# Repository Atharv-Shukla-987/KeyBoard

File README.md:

# mech_board
## Introduction
It is compact wireless custum mechanical keyboard based on rasberry pi pico w with a 0.96 Oled display for displaying battery percentage and with a slider[linear potential meter] for music control and some DJ vibes, yes a slider not a rotary encoder because for some reason i just don't like rotary encoders. It has battery of 2000 mah . It can act as wired and wireless keyboard , both . I have a slider switch for changing the mode . It got two holes on its case wall one for charging port and other for pico port . I have also used RGBs for some asthetics. My pc does not have in built blutooth so , I have also made a reciever dougle.
## Components Used
### kerboard
 1.I have used raspberry pi pico w over others because beacause of high number of gpio pins and is easily programable and also is bluetooth and wifi for good contectivity
 2. A TP4050 [charging module] for charging battery
 
 3. A mcp1700 [voltage regulator] for converting 3.7v from battery to 5v requried from raspberry pi pico w
 
 4.A 1N4148 Diode so that ghosting do not occurs 

 5. A oled display 128x64 i2c for checking battery and making keyboard more intresting

 6. A SK6812 MINI for lightening and vibe

 7. A female Usb type C for charging 

 8. A 3.7V 2000mah lipo battery for increased battery life

 9. keycaps from meckeys

 10. custum pcb
 
 11. 3d printed case
 
 12. cherry x switches
 
 13. Capacitors and registors 

### reciever 

1.esp32 mini s3 for conecting with keyboard 

2. USb type A

3. MCP1700 voltage regulator

# RECIEVER

## schematics

## PCB layout

## 3d

### Front

### Back

# KEYBOARD

## schematic

## PCB layout

## 3D 
### front

### back Model

## footprints

## Case

### Top case

### Bottom case

### Assembled case

# BOM 

https://docs.google.com/spreadsheets/d/1NN-7fyjT-_NMtKUpMZtBps8UBcZRbg7seoi4lXChdCc/edit?usp=sharing

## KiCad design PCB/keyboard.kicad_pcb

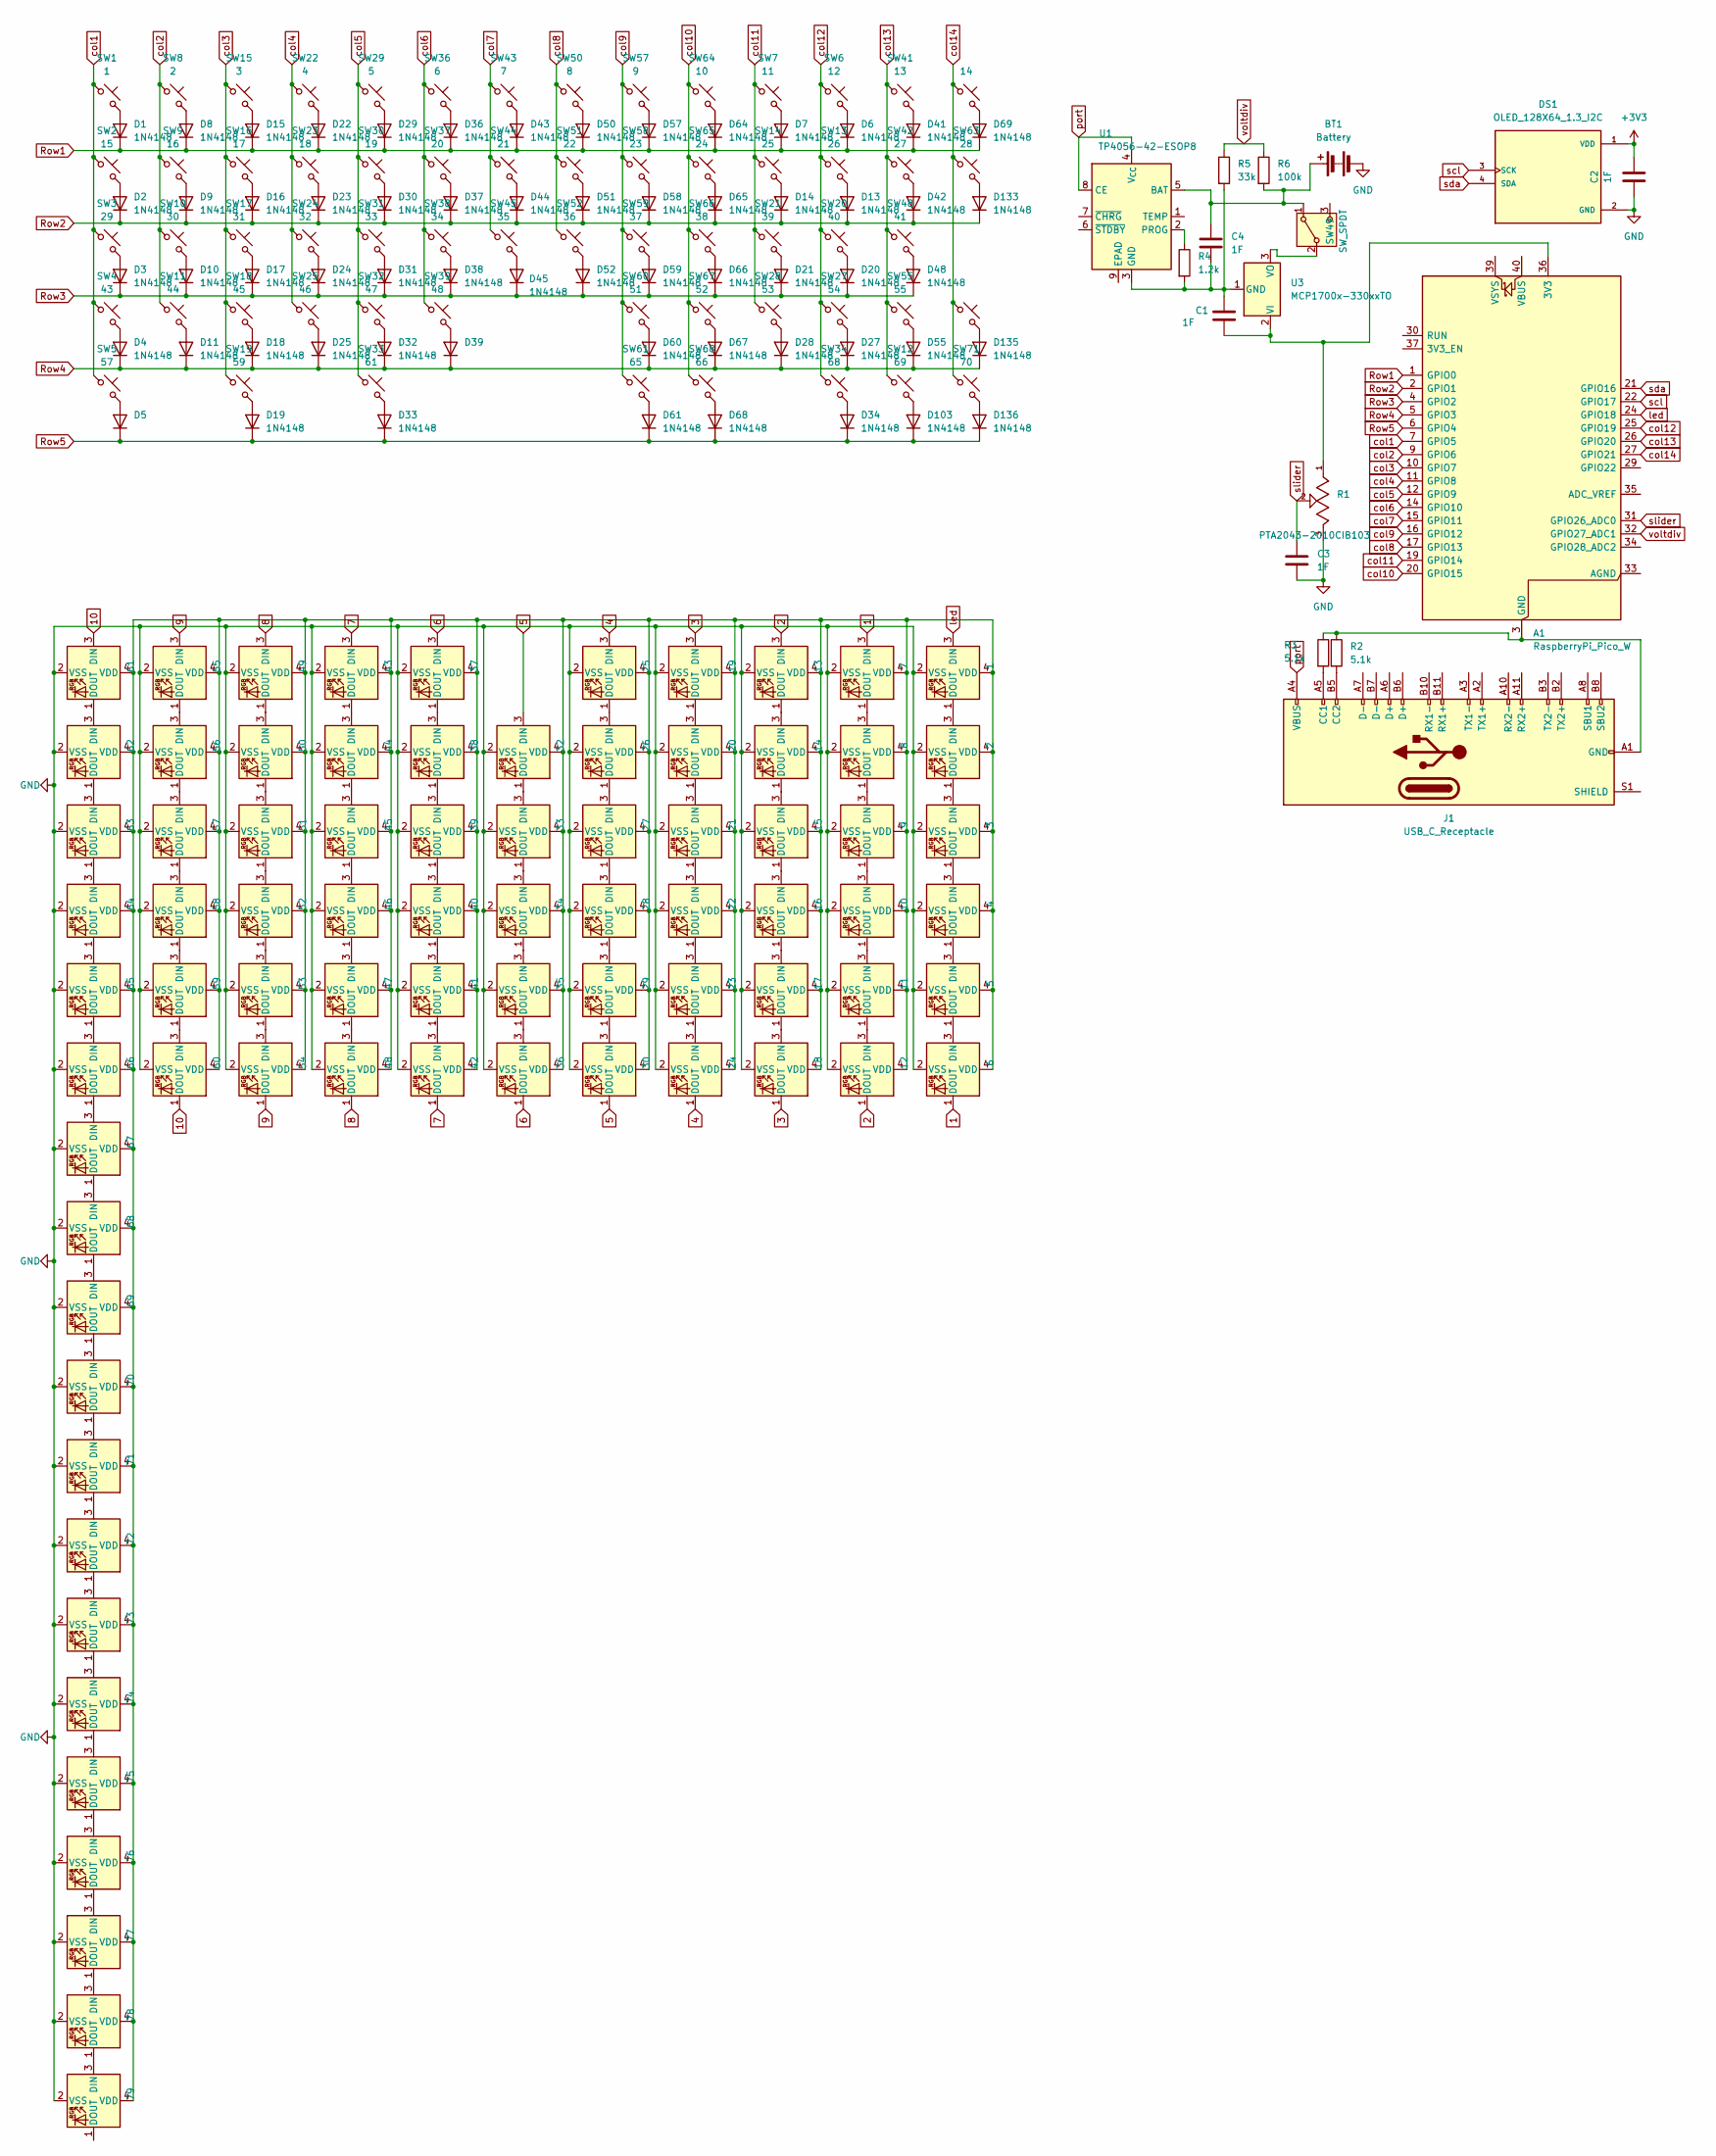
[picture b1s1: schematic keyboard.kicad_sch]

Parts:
A1: RaspberryPi_Pico_W; RaspberryPi_Pico_W_SMD_HandSolder
BT1: Battery; JST_XH_B2B-XH-AM_1x02_P2.50mm_Vertical
C1, C2, C3, C4: 1F; C_0805_2012Metric
D1, D2, D3, D4, D5, D6, D7, D8, D9, D10, D11, D13, D14, D15, D16, D17, D18, D19, D20, D21, D22, D23, D24, D25, D27, D28, D29, D30, D31, D32, D33, D34, D36, D37, D38, D39, D41, D42, D43, D44, D45, D48, D50, D51, D52, D55, D57, D58, D59, D60, D61, D64, D65, D66, D67, D68, D69, D103, D133, D135, D136: 1N4148; D_DO-35_SOD27_P7.62mm_Horizontal
D12: 67; SK6812MINI-E_fixed
D26: 68; SK6812MINI-E_fixed
D35: 69; SK6812MINI-E_fixed
D40: 70; SK6812MINI-E_fixed
D46: 71; SK6812MINI-E_fixed
D47: 72; SK6812MINI-E_fixed
D49: 7; SK6812MINI-E_fixed
D53: 73; SK6812MINI-E_fixed
D54: 74; SK6812MINI-E_fixed
D56: 8; SK6812MINI-E_fixed
D62: 75; SK6812MINI-E_fixed
D63: 9; SK6812MINI-E_fixed
D70: 10; SK6812MINI-E_fixed
D71: 1; SK6812MINI-E_fixed
D72: 2; SK6812MINI-E_fixed
D73: 3; SK6812MINI-E_fixed
D74: 4; SK6812MINI-E_fixed
D75: 5; SK6812MINI-E_fixed
D76: 6; SK6812MINI-E_fixed
D77: 11; SK6812MINI-E_fixed
D78: 12; SK6812MINI-E_fixed
D79: 19; SK6812MINI-E_fixed
D80: 20; SK6812MINI-E_fixed
D81: 21; SK6812MINI-E_fixed
D82: 22; SK6812MINI-E_fixed
D83: 23; SK6812MINI-E_fixed
D84: 24; SK6812MINI-E_fixed
D85: 13; SK6812MINI-E_fixed
D86: 14; SK6812MINI-E_fixed
D87: 15; SK6812MINI-E_fixed
D88: 16; SK6812MINI-E_fixed
D89: 17; SK6812MINI-E_fixed
D90: 18; SK6812MINI-E_fixed
D91: 43; SK6812MINI-E_fixed
D92: 44; SK6812MINI-E_fixed
D93: 45; SK6812MINI-E_fixed
D94: 46; SK6812MINI-E_fixed
D95: 47; SK6812MINI-E_fixed
D96: 48; SK6812MINI-E_fixed
D97: 37; SK6812MINI-E_fixed
D98: 38; SK6812MINI-E_fixed
D99: 39; SK6812MINI-E_fixed
D100: 40; SK6812MINI-E_fixed
D101: 41; SK6812MINI-E_fixed
D102: 42; SK6812MINI-E_fixed
D104: 32; SK6812MINI-E_fixed
D105: 33; SK6812MINI-E_fixed
D106: 34; SK6812MINI-E_fixed
D107: 35; SK6812MINI-E_fixed
D108: 36; SK6812MINI-E_fixed
D109: 25; SK6812MINI-E_fixed
D110: 26; SK6812MINI-E_fixed
D111: 27; SK6812MINI-E_fixed
D112: 28; SK6812MINI-E_fixed
D113: 29; SK6812MINI-E_fixed
D114: 30; SK6812MINI-E_fixed
D115: 61; SK6812MINI-E_fixed
D116: 62; SK6812MINI-E_fixed
D117: 63; SK6812MINI-E_fixed
D118: 64; SK6812MINI-E_fixed
D119: 65; SK6812MINI-E_fixed
D120: 66; SK6812MINI-E_fixed
D121: 55; SK6812MINI-E_fixed
D122: 56; SK6812MINI-E_fixed
D123: 57; SK6812MINI-E_fixed
D124: 58; SK6812MINI-E_fixed
D125: 59; SK6812MINI-E_fixed
D126: 60; SK6812MINI-E_fixed
D127: 49; SK6812MINI-E_fixed
D128: 50; SK6812MINI-E_fixed
D129: 51; SK6812MINI-E_fixed
D130: 52; SK6812MINI-E_fixed
D131: 53; SK6812MINI-E_fixed
D132: 54; SK6812MINI-E_fixed
D134: 76; SK6812MINI-E_fixed
D137: 77; SK6812MINI-E_fixed
D138: 78; SK6812MINI-E_fixed
D139: 79; SK6812MINI-E_fixed
DS1: OLED_128X64_1.3_I2C; LCD_OLED_128X64_1.3_I2C; PARTREV NA
J1: USB_C_Receptacle; USB_C_Receptacle_Molex_105450-0101
R1: PTA2043-2010CIB103; TRIM_PTA4543-2010CPB103; PARTREV 04/21
R2, R3: 5.1k; R_0805_2012Metric
R4: 1.2k; R_0805_2012Metric
R5: 33k; R_0805_2012Metric
R6: 100k; R_0805_2012Metric
SW1: 1; SW_Cherry_MX1A_1.00u_PCB
SW2: 15; SW_Cherry_MX1A_1.50u_PCB
SW3: 29; SW_Cherry_MX1A_1.75u_PCB
SW4: 43; SW_Cherry_MX1A_2.25u_PCB
SW5: 57; SW_Cherry_MX1A_1.25u_PCB
SW6: 12; SW_Cherry_MX1A_1.00u_PCB
SW7: 11; SW_Cherry_MX1A_1.00u_PCB
SW8: 2; SW_Cherry_MX1A_1.00u_PCB
SW9: 16; SW_Cherry_MX1A_1.00u_PCB
SW10: 30; SW_Cherry_MX1A_1.00u_PCB
SW11: 44; SW_Cherry_MX1A_1.00u_PCB
SW12: 69; SW_Cherry_MX1A_1.25u_PCB
SW13: 26; SW_Cherry_MX1A_1.00u_PCB
SW14: 25; SW_Cherry_MX1A_1.00u_PCB
SW15: 3; SW_Cherry_MX1A_1.00u_PCB
SW16: 17; SW_Cherry_MX1A_1.00u_PCB
SW17: 31; SW_Cherry_MX1A_1.00u_PCB
SW18: 45; SW_Cherry_MX1A_1.00u_PCB
SW19: 59; SW_Cherry_MX1A_1.25u_PCB
SW20: 40; SW_Cherry_MX1A_1.00u_PCB
SW21: 39; SW_Cherry_MX1A_1.00u_PCB
SW22: 4; SW_Cherry_MX1A_1.00u_PCB
SW23: 18; SW_Cherry_MX1A_1.00u_PCB
SW24: 32; SW_Cherry_MX1A_1.00u_PCB
SW25: 46; SW_Cherry_MX1A_1.00u_PCB
SW27: 54; SW_Cherry_MX1A_1.00u_PCB
SW28: 53; SW_Cherry_MX1A_1.00u_PCB
SW29: 5; SW_Cherry_MX1A_1.00u_PCB
SW30: 19; SW_Cherry_MX1A_1.00u_PCB
SW31: 33; SW_Cherry_MX1A_1.00u_PCB
SW32: 47; SW_Cherry_MX1A_1.00u_PCB
SW33: 61; SW_Cherry_MX1A_1.25u_PCB
SW34: 68; SW_Cherry_MX1A_1.25u_PCB
SW36: 6; SW_Cherry_MX1A_1.00u_PCB
SW37: 20; SW_Cherry_MX1A_1.00u_PCB
SW38: 34; SW_Cherry_MX1A_1.00u_PCB
SW39: 48; SW_Cherry_MX1A_1.00u_PCB
SW41: 13; SW_Cherry_MX1A_1.00u_PCB
SW42: 27; SW_Cherry_MX1A_1.00u_PCB
SW43: 7; SW_Cherry_MX1A_1.00u_PCB
SW44: 21; SW_Cherry_MX1A_1.00u_PCB
SW45: 35; SW_Cherry_MX1A_1.00u_PCB
SW48: 41; SW_Cherry_MX1A_2.25u_PCB
SW49: SW_SPDT; SW_Slide_1P2T_CK_OS102011MS2Q
SW50: 8; SW_Cherry_MX1A_1.00u_PCB
SW51: 22; SW_Cherry_MX1A_1.00u_PCB
SW52: 36; SW_Cherry_MX1A_1.00u_PCB
SW55: 55; SW_Cherry_MX1A_1.00u_PCB
SW57: 9; SW_Cherry_MX1A_1.00u_PCB
SW58: 23; SW_Cherry_MX1A_1.00u_PCB
SW59: 37; SW_Cherry_MX1A_1.00u_PCB
SW60: 51; SW_Cherry_MX1A_1.00u_PCB
SW61: 65; SW_Cherry_MX1A_6.25u_PCB
SW62: 14; SW_Cherry_MX1A_2.00u_PCB
SW63: 28; SW_Cherry_MX1A_1.50u_PCB
SW64: 10; SW_Cherry_MX1A_1.00u_PCB
SW65: 24; SW_Cherry_MX1A_1.00u_PCB
SW66: 38; SW_Cherry_MX1A_1.00u_PCB
SW67: 52; SW_Cherry_MX1A_1.00u_PCB
SW68: 66; SW_Cherry_MX1A_1.25u_PCB
SW70: 56; SW_Cherry_MX1A_2.75u_PCB
SW71: 70; SW_Cherry_MX1A_1.25u_PCB
U1: TP4056-42-ESOP8; SOIC-8-1EP_3.9x4.9mm_P1.27mm_EP2.41x3.3mm_ThermalVias
U3: MCP1700x-330xxTO; TO-92_Inline

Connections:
1: D49.3 (DIN), D76.1 (DOUT)
2: D78.1 (DOUT), D85.3 (DIN)
3: D79.3 (DIN), D90.1 (DOUT)
4: D84.1 (DOUT), D109.3 (DIN)
5: D104.3 (DIN), D114.1 (DOUT)
6: D97.3 (DIN), D108.1 (DOUT)
7: D91.3 (DIN), D102.1 (DOUT)
8: D96.1 (DOUT), D127.3 (DIN)
9: D121.3 (DIN), D132.1 (DOUT)
10: D115.3 (DIN), D126.1 (DOUT)
+3V3: C2.1, DS1.1 (VDD)
<NO NET>: D12.4 (VDD), D26.4 (VDD), D35.4 (VDD), D40.4 (VDD), D46.4 (VDD), D47.4 (VDD), D49.4 (VDD), D53.4 (VDD), D54.4 (VDD), D56.4 (VDD), D62.4 (VDD), D63.4 (VDD), D70.4 (VDD), D71.4 (VDD), D72.4 (VDD), D73.4 (VDD), D74.4 (VDD), D75.4 (VDD), D76.4 (VDD), D77.4 (VDD), D78.4 (VDD), D79.4 (VDD), D80.4 (VDD), D81.4 (VDD), D82.4 (VDD), D83.4 (VDD), D84.4 (VDD), D85.4 (VDD), D86.4 (VDD), D87.4 (VDD), D88.4 (VDD), D89.4 (VDD), D90.4 (VDD), D91.4 (VDD), D92.4 (VDD), D93.4 (VDD), D94.4 (VDD), D95.4 (VDD), D96.4 (VDD), D97.4 (VDD), D98.4 (VDD), D99.4 (VDD), D100.4 (VDD), D101.4 (VDD), D102.4 (VDD), D104.4 (VDD), D105.4 (VDD), D106.4 (VDD), D107.4 (VDD), D108.4 (VDD), D109.4 (VDD), D110.4 (VDD), D111.4 (VDD), D112.4 (VDD), D113.4 (VDD), D114.4 (VDD), D115.4 (VDD), D116.4 (VDD), D117.4 (VDD), D118.4 (VDD), D119.4 (VDD), D120.4 (VDD), D121.4 (VDD), D122.4 (VDD), D123.4 (VDD), D124.4 (VDD), D125.4 (VDD), D126.4 (VDD), D127.4 (VDD), D128.4 (VDD), D129.4 (VDD), D130.4 (VDD), D131.4 (VDD), D132.4 (VDD), D134.4 (VDD), D137.4 (VDD), D138.4 (VDD), D139.4 (VDD)
GND: BT1.2 (-), C2.2, C3.2, D12.2 (VSS), D26.2 (VSS), D35.2 (VSS), D40.2 (VSS), D46.2 (VSS), D47.2 (VSS), D49.2 (VSS), D53.2 (VSS), D54.2 (VSS), D56.2 (VSS), D62.2 (VSS), D63.2 (VSS), D70.2 (VSS), D71.2 (VSS), D72.2 (VSS), D73.2 (VSS), D74.2 (VSS), D75.2 (VSS), D76.2 (VSS), D77.2 (VSS), D78.2 (VSS), D79.2 (VSS), D80.2 (VSS), D81.2 (VSS), D82.2 (VSS), D83.2 (VSS), D84.2 (VSS), D85.2 (VSS), D86.2 (VSS), D87.2 (VSS), D88.2 (VSS), D89.2 (VSS), D90.2 (VSS), D91.2 (VSS), D92.2 (VSS), D93.2 (VSS), D94.2 (VSS), D95.2 (VSS), D96.2 (VSS), D97.2 (VSS), D98.2 (VSS), D99.2 (VSS), D100.2 (VSS), D101.2 (VSS), D102.2 (VSS), D104.2 (VSS), D105.2 (VSS), D106.2 (VSS), D107.2 (VSS), D108.2 (VSS), D109.2 (VSS), D110.2 (VSS), D111.2 (VSS), D112.2 (VSS), D113.2 (VSS), D114.2 (VSS), D115.2 (VSS), D116.2 (VSS), D117.2 (VSS), D118.2 (VSS), D119.2 (VSS), D120.2 (VSS), D121.2 (VSS), D122.2 (VSS), D123.2 (VSS), D124.2 (VSS), D125.2 (VSS), D126.2 (VSS), D127.2 (VSS), D128.2 (VSS), D129.2 (VSS), D130.2 (VSS), D131.2 (VSS), D132.2 (VSS), D134.2 (VSS), D137.2 (VSS), D138.2 (VSS), D139.2 (VSS), DS1.2 (GND), R1.3
unnamed: A1.36 (3V3), C1.2, R1.1, U3.2 (VI)
unnamed: A1.3 (GND), A1.8 (GND), A1.13 (GND), A1.18 (GND), A1.23 (GND), A1.28 (GND), A1.38 (GND), J1.A1 (GND), J1.A12 (GND), J1.B1 (GND), J1.B12 (GND), R2.1, R3.1
unnamed: BT1.1 (+), C4.1, R6.2, SW49.1 (A), U1.5 (BAT)
unnamed: D1.2 (A), SW1.2
unnamed: D2.2 (A), SW2.2
unnamed: D3.2 (A), SW3.2
unnamed: D4.2 (A), SW4.2
unnamed: D5.2 (A), SW5.2
unnamed: D6.2 (A), SW6.2
unnamed: D7.2 (A), SW7.2
unnamed: D8.2 (A), SW8.2
unnamed: D9.2 (A), SW9.2
unnamed: D10.2 (A), SW10.2
unnamed: D11.2 (A), SW11.2
unnamed: D12.3 (DIN), D120.1 (DOUT)
unnamed: D12.1 (DOUT), D26.3 (DIN)
unnamed: D13.2 (A), SW13.2
unnamed: D14.2 (A), SW14.2
unnamed: D15.2 (A), SW15.2
unnamed: D16.2 (A), SW16.2
unnamed: D17.2 (A), SW17.2
unnamed: D18.2 (A), SW18.2
unnamed: D19.2 (A), SW19.2
unnamed: D20.2 (A), SW20.2
unnamed: D21.2 (A), SW21.2
unnamed: D22.2 (A), SW22.2
unnamed: D23.2 (A), SW23.2
unnamed: D24.2 (A), SW24.2
unnamed: D25.2 (A), SW25.2
unnamed: D26.1 (DOUT), D35.3 (DIN)
unnamed: D27.2 (A), SW27.2
unnamed: D28.2 (A), SW28.2
unnamed: D29.2 (A), SW29.2
unnamed: D30.2 (A), SW30.2
unnamed: D31.2 (A), SW31.2
unnamed: D32.2 (A), SW32.2
unnamed: D33.2 (A), SW33.2
unnamed: D34.2 (A), SW34.2
unnamed: D35.1 (DOUT), D40.3 (DIN)
unnamed: D36.2 (A), SW36.2
unnamed: D37.2 (A), SW37.2
unnamed: D38.2 (A), SW38.2
unnamed: D39.2 (A), SW39.2
unnamed: D40.1 (DOUT), D46.3 (DIN)
unnamed: D41.2 (A), SW41.2
unnamed: D42.2 (A), SW42.2
unnamed: D43.2 (A), SW43.2
unnamed: D44.2 (A), SW44.2
unnamed: D45.2 (A), SW45.2
unnamed: D46.1 (DOUT), D47.3 (DIN)
unnamed: D47.1 (DOUT), D53.3 (DIN)
unnamed: D48.2 (A), SW48.2
unnamed: D49.1 (DOUT), D56.3 (DIN)
unnamed: D50.2 (A), SW50.2
unnamed: D51.2 (A), SW51.2
unnamed: D52.2 (A), SW52.2
unnamed: D53.1 (DOUT), D54.3 (DIN)
unnamed: D54.1 (DOUT), D62.3 (DIN)
unnamed: D55.2 (A), SW55.2
unnamed: D56.1 (DOUT), D63.3 (DIN)
unnamed: D57.2 (A), SW57.2
unnamed: D58.2 (A), SW58.2
unnamed: D59.2 (A), SW59.2
unnamed: D60.2 (A), SW60.2
unnamed: D61.2 (A), SW61.2
unnamed: D63.1 (DOUT), D70.3 (DIN)
unnamed: D64.2 (A), SW64.2
unnamed: D65.2 (A), SW65.2
unnamed: D66.2 (A), SW66.2
unnamed: D67.2 (A), SW67.2
unnamed: D68.2 (A), SW68.2
unnamed: D69.2 (A), SW62.2
unnamed: D70.1 (DOUT), D77.3 (DIN)
unnamed: D71.1 (DOUT), D72.3 (DIN)
unnamed: D72.1 (DOUT), D73.3 (DIN)
unnamed: D73.1 (DOUT), D74.3 (DIN)
unnamed: D74.1 (DOUT), D75.3 (DIN)
unnamed: D75.1 (DOUT), D76.3 (DIN)
unnamed: D77.1 (DOUT), D78.3 (DIN)
unnamed: D79.1 (DOUT), D80.3 (DIN)
unnamed: D80.1 (DOUT), D81.3 (DIN)
unnamed: D81.1 (DOUT), D82.3 (DIN)
unnamed: D82.1 (DOUT), D83.3 (DIN)
unnamed: D83.1 (DOUT), D84.3 (DIN)
unnamed: D85.1 (DOUT), D86.3 (DIN)
unnamed: D86.1 (DOUT), D87.3 (DIN)
unnamed: D87.1 (DOUT), D88.3 (DIN)
unnamed: D88.1 (DOUT), D89.3 (DIN)
unnamed: D89.1 (DOUT), D90.3 (DIN)
unnamed: D91.1 (DOUT), D92.3 (DIN)
unnamed: D92.1 (DOUT), D93.3 (DIN)
unnamed: D93.1 (DOUT), D94.3 (DIN)
unnamed: D94.1 (DOUT), D95.3 (DIN)
unnamed: D95.1 (DOUT), D96.3 (DIN)
unnamed: D97.1 (DOUT), D98.3 (DIN)
unnamed: D98.1 (DOUT), D99.3 (DIN)
unnamed: D99.1 (DOUT), D100.3 (DIN)
unnamed: D100.1 (DOUT), D101.3 (DIN)
unnamed: D101.1 (DOUT), D102.3 (DIN)
unnamed: D103.2 (A), SW12.2
unnamed: D104.1 (DOUT), D105.3 (DIN)
unnamed: D105.1 (DOUT), D106.3 (DIN)
unnamed: D106.1 (DOUT), D107.3 (DIN)
unnamed: D107.1 (DOUT), D108.3 (DIN)
unnamed: D109.1 (DOUT), D110.3 (DIN)
unnamed: D110.1 (DOUT), D111.3 (DIN)
unnamed: D111.1 (DOUT), D112.3 (DIN)
unnamed: D112.1 (DOUT), D113.3 (DIN)
unnamed: D113.1 (DOUT), D114.3 (DIN)
unnamed: D115.1 (DOUT), D116.3 (DIN)
unnamed: D116.1 (DOUT), D117.3 (DIN)
unnamed: D117.1 (DOUT), D118.3 (DIN)
unnamed: D118.1 (DOUT), D119.3 (DIN)
unnamed: D119.1 (DOUT), D120.3 (DIN)
unnamed: D121.1 (DOUT), D122.3 (DIN)
unnamed: D122.1 (DOUT), D123.3 (DIN)
unnamed: D123.1 (DOUT), D124.3 (DIN)
unnamed: D124.1 (DOUT), D125.3 (DIN)
unnamed: D125.1 (DOUT), D126.3 (DIN)
unnamed: D127.1 (DOUT), D128.3 (DIN)
unnamed: D128.1 (DOUT), D129.3 (DIN)
unnamed: D129.1 (DOUT), D130.3 (DIN)
unnamed: D130.1 (DOUT), D131.3 (DIN)
unnamed: D131.1 (DOUT), D132.3 (DIN)
unnamed: D133.2 (A), SW63.2
unnamed: D62.1 (DOUT), D134.3 (DIN)
unnamed: D134.1 (DOUT), D137.3 (DIN)
unnamed: D135.2 (A), SW70.2
unnamed: D136.2 (A), SW71.2
unnamed: D137.1 (DOUT), D138.3 (DIN)
unnamed: D138.1 (DOUT), D139.3 (DIN)
unnamed: J1.A5 (CC1), R3.2
unnamed: J1.B5 (CC2), R2.2
unnamed: SW49.2 (B), U3.3 (VO)
unnamed: C1.1, C4.2, R4.2, R5.2, U1.3 (GND), U3.1 (GND)
unnamed: R4.1, U1.2 (PROG)
Row1: A1.1 (GPIO0), D1.1 (K), D6.1 (K), D7.1 (K), D8.1 (K), D15.1 (K), D22.1 (K), D29.1 (K), D36.1 (K), D41.1 (K), D43.1 (K), D50.1 (K), D57.1 (K), D64.1 (K), D69.1 (K)
Row2: A1.2 (GPIO1), D2.1 (K), D9.1 (K), D13.1 (K), D14.1 (K), D16.1 (K), D23.1 (K), D30.1 (K), D37.1 (K), D42.1 (K), D44.1 (K), D51.1 (K), D58.1 (K), D65.1 (K), D133.1 (K)
Row3: A1.4 (GPIO2), D3.1 (K), D10.1 (K), D17.1 (K), D20.1 (K), D21.1 (K), D24.1 (K), D31.1 (K), D38.1 (K), D45.1 (K), D48.1 (K), D52.1 (K), D59.1 (K), D66.1 (K)
Row4: A1.5 (GPIO3), D4.1 (K), D11.1 (K), D18.1 (K), D25.1 (K), D27.1 (K), D28.1 (K), D32.1 (K), D39.1 (K), D55.1 (K), D60.1 (K), D67.1 (K), D135.1 (K)
Row5: A1.6 (GPIO4), D5.1 (K), D19.1 (K), D33.1 (K), D34.1 (K), D61.1 (K), D68.1 (K), D103.1 (K), D136.1 (K)
col1: A1.7 (GPIO5), SW1.1, SW2.1, SW3.1, SW4.1, SW5.1
col2: A1.9 (GPIO6), SW8.1, SW9.1, SW10.1, SW11.1
col3: A1.10 (GPIO7), SW15.1, SW16.1, SW17.1, SW18.1, SW19.1
col4: A1.11 (GPIO8), SW22.1, SW23.1, SW24.1, SW25.1
col5: A1.12 (GPIO9), SW29.1, SW30.1, SW31.1, SW32.1, SW33.1
col6: A1.14 (GPIO10), SW36.1, SW37.1, SW38.1, SW39.1
col7: A1.15 (GPIO11), SW43.1, SW44.1, SW45.1
col8: A1.17 (GPIO13), SW50.1, SW51.1, SW52.1
col9: A1.16 (GPIO12), SW57.1, SW58.1, SW59.1, SW60.1, SW61.1
col10: A1.20 (GPIO15), SW64.1, SW65.1, SW66.1, SW67.1, SW68.1
col11: A1.19 (GPIO14), SW7.1, SW14.1, SW21.1, SW28.1
col12: A1.25 (GPIO19), SW6.1, SW13.1, SW20.1, SW27.1, SW34.1
col13: A1.26 (GPIO20), SW12.1, SW41.1, SW42.1, SW48.1, SW55.1
col14: A1.27 (GPIO21), SW62.1, SW63.1, SW70.1, SW71.1
led: A1.24 (GPIO18), D71.3 (DIN)
port: J1.A4 (VBUS), J1.A9 (VBUS), J1.B4 (VBUS), J1.B9 (VBUS), U1.4 (V_{CC}), U1.8 (CE)
scl: A1.22 (GPIO17), DS1.3 (SCK)
sda: A1.21 (GPIO16), DS1.4 (SDA)
slider: A1.31 (GPIO26_ADC0), C3.1, R1.2
voltdiv: A1.32 (GPIO27_ADC1), R5.1, R6.1

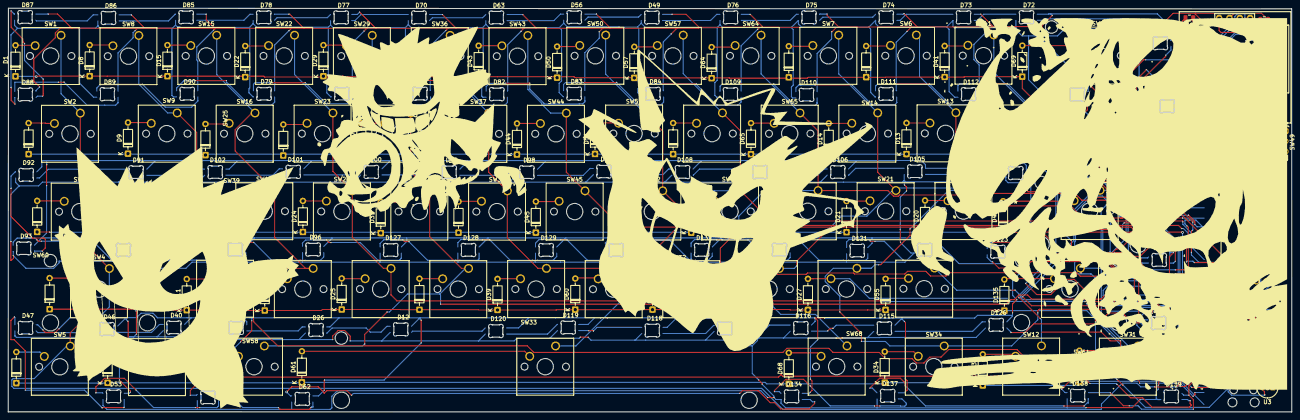
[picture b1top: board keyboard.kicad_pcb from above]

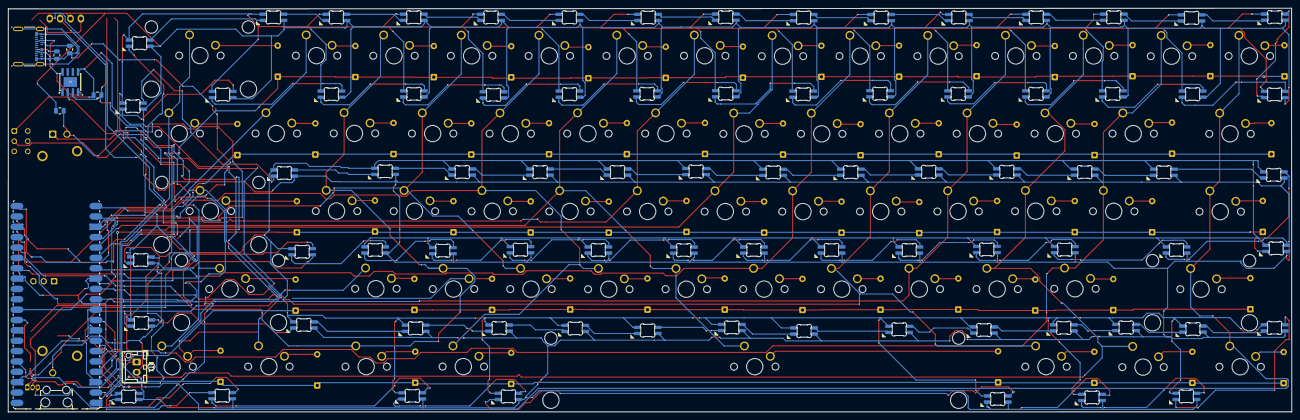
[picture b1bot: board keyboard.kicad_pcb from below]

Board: 2 copper layers, 314.8 x 99.0 mm, 217 parts (8 on the bottom side), 174 nets.

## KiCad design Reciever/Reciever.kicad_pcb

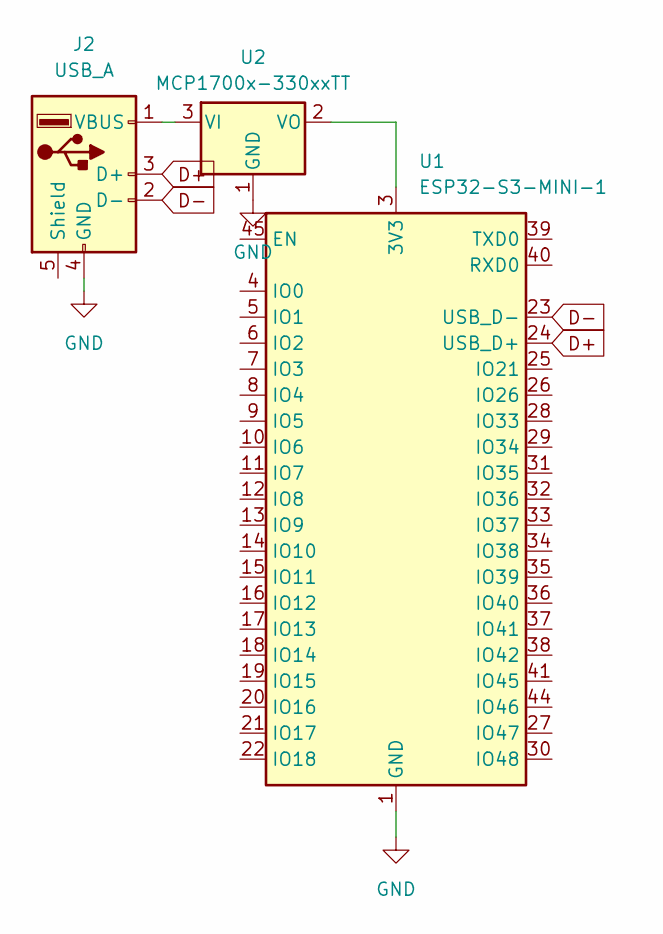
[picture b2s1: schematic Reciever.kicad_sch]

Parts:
J2: USB_A; USB_A_Molex_67643_Horizontal
U1: ESP32-S3-MINI-1; ESP32-S2-MINI-1
U2: MCP1700x-330xxTT; SOT-23

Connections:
D+: J2.3 (D+), U1.24 (USB_D+)
D-: J2.2 (D-), U1.23 (USB_D-)
GND: J2.4 (GND), U1.1 (GND), U1.2 (GND), U1.42 (GND), U1.43 (GND), U1.46 (GND), U1.47 (GND), U1.48 (GND), U1.49 (GND), U1.50 (GND), U1.51 (GND), U1.52 (GND), U1.53 (GND), U1.54 (GND), U1.55 (GND), U1.56 (GND), U1.57 (GND), U1.58 (GND), U1.59 (GND), U1.60 (GND), U1.61 (GND), U1.62 (GND), U1.63 (GND), U1.64 (GND), U1.65 (GND), U2.1 (GND)
unnamed: J2.1 (VBUS), U2.3 (VI)
unnamed: U1.3 (3V3), U2.2 (VO)

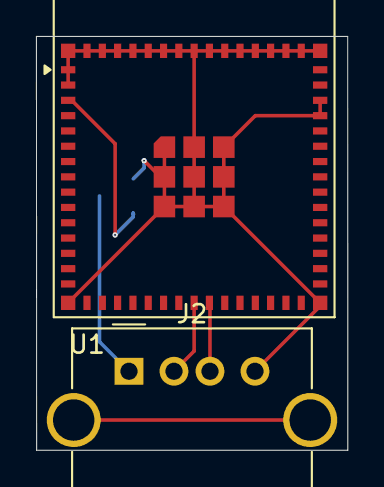
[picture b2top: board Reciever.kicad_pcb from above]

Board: 2 copper layers, 17.3 x 23.0 mm, 3 parts (1 on the bottom side), 5 nets.

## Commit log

2026-05-24 keyboard
2026-05-28 hiojb
2026-05-28 yyyyyyyytv6g
2026-05-29 UPDATING RECIEVER
2026-05-29 code
2026-06-02 Add new schematic image to README
    Added a new schematic image for the receiver section.
2026-06-02 Update README with new images for schematics and PCB
    Added additional schematic and PCB layout images for the keyboard.
2026-06-02 Document BOM creation and part selection challenges
    Added details about the BOM creation process and challenges faced during part selection.
2026-06-02 Rename journal.md to JOURNAL.md
2026-06-02 Refactor JOURNAL.md for improved readability
2026-06-02 Revise JOURNAL.md with time tracking and formatting fixes
    Updated JOURNAL.md to include total time spent on each section and corrected formatting issues.
2026-06-02 Update JOURNAL.md with project time and PCB design details
    Added total time spent on the project and detailed PCB design process.
2026-06-05 gonna write code myself but latter
